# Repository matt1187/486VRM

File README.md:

# Project  486VRM.
A interposer for  3.3V 486  for using on motherboard without 3.3V regulator.
A advantage of this  486VRM interposer: switching regulator instead linear regulator. -> less heating.

# PCB Revision History
- 000 initial draft
- 001 smaller pcb size, current limit resistor added for Intel DX4 I/O buffer (pin J1), added solder help

# Feartures
- Vcore can be adjusting with jumper: 3.3V,  3.45 and 4V
- Clock-Multi jumper (for some DX4 and AMD/Cyrix 5x86)
- Writeback L1 jumper 
- connector for fan, 5V

# Pictures & how to soldering of pin
- I use "BGA"-technologie on this interposer.

- using of solder paste is very recommend.
- you need solder iron with long and small chisel for extra adding of tin to socket.

- "solder helper hold pin (bottom) on their place.
- very recommend: solder only one row with pin to pcb, then second row, then third row.

# Bill of material
[

|Footprint|Count|Value|Supplier|Order-number|
|--------------|----|-----|-------|-----------------|
|Top1|1|486|various|PGA-168 486 168pin socket|
|Bot1|1|486|various| turned pin header, dia =0.5mm|
|JP1|1|WB/WT|Digikey|609-78511-203HLF-ND|
|JP2|1|voltage|Digikey|609-78511-203HLF-ND|
|JP3|1|CLKMUL|Digikey|609-78511-203HLF-ND|
|JP4|1|FAN|Digikey|609-78511-203HLF-ND|
|U1|1|TPS54308DDCR|Digikey|296-47880-1-ND|
|R1|1|50Ω|Digikey|541-CRCW080550R0FKTACT-ND |
|R2|1|100kΩ|Digikey|311-100KARCT-ND |
|R3|1|22kΩ|Digikey|311-22KARCT-ND|
|R4|1|430kΩ|Digikey|311-430KARCT-ND |
|R5|1|91kΩ|Digikey|311-91KARCT-ND |
|R6|1|100Ω|Digikey|603-RC0805JR-07100RL|
|C4,C3,C2,C1|4|10µF|Digikey|399-C1206C106M3PAC7210CT-ND |
|C6|1|75pf|Digikey|478-3743-1-ND|
|C10,C9,C8,C7,C5|5|0.1µF|Digikey|KGM21NR71H104KT|
|C11|1|47µF|Digikey|T491C476M010AT|
|L1|1|10µh|Digikey|LMLP07A7M100DTAS |

# License
The project is free for non-commercial reproduction. Do not sell it on Ebay or other platforms for profit. Do not make a closed source derivative. Share your experiences and ideas with the community.

This work is licensed under a [Creative Commons Attribution-NonCommercial-ShareAlike 4.0 International License][cc-by-nc-sa].

[![CC BY-NC-SA 4.0][cc-by-nc-sa-image]][cc-by-nc-sa]

[cc-by-nc-sa]: http://creativecommons.org/licenses/by-nc-sa/4.0/
[cc-by-nc-sa-image]: https://licensebuttons.net/l/by-nc-sa/4.0/88x31.png

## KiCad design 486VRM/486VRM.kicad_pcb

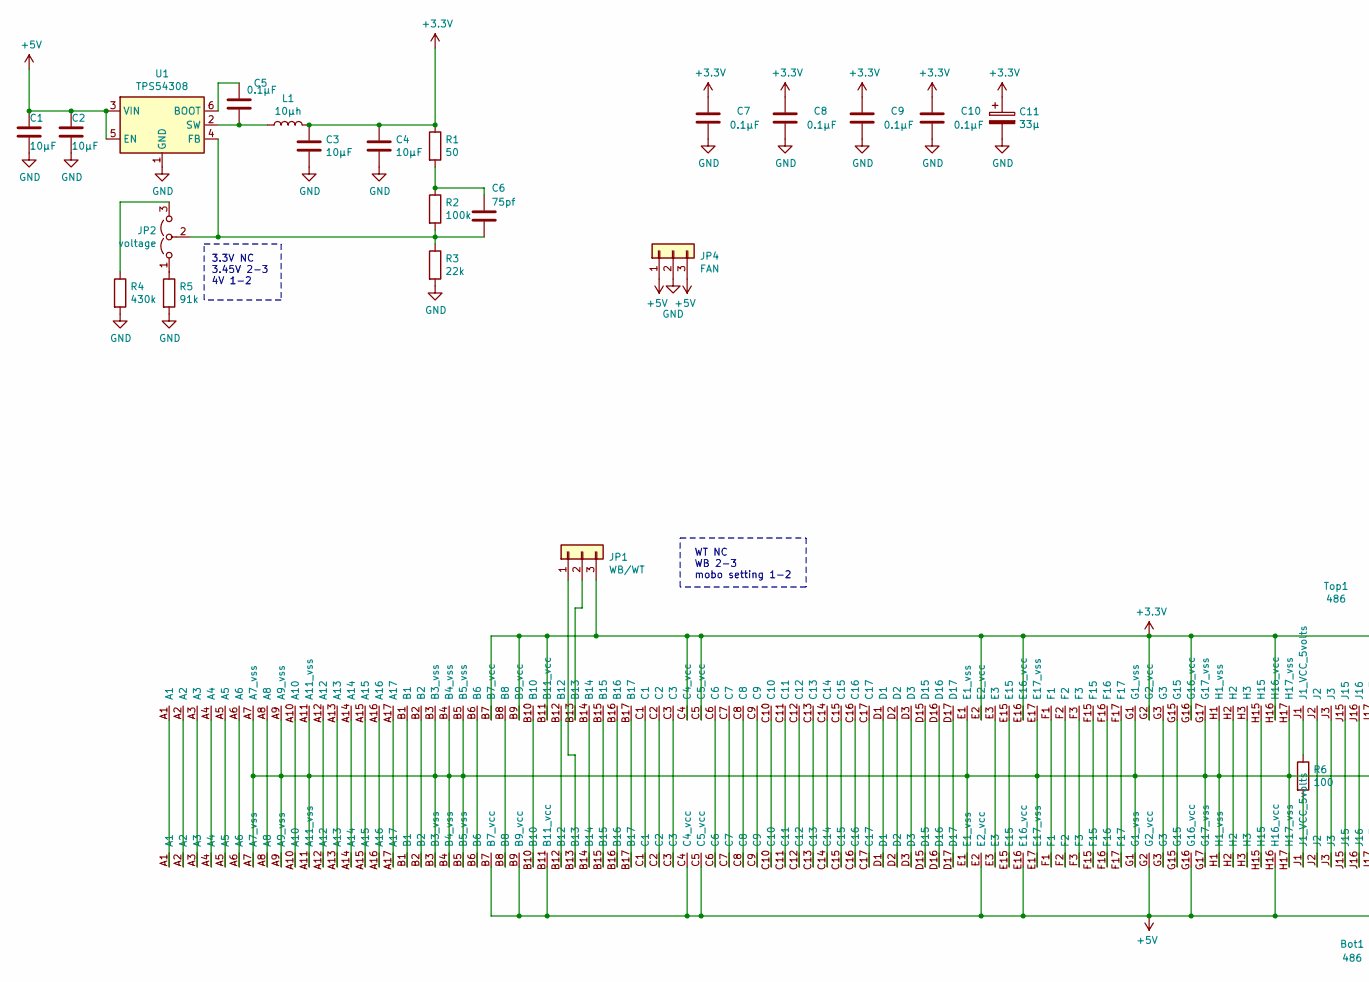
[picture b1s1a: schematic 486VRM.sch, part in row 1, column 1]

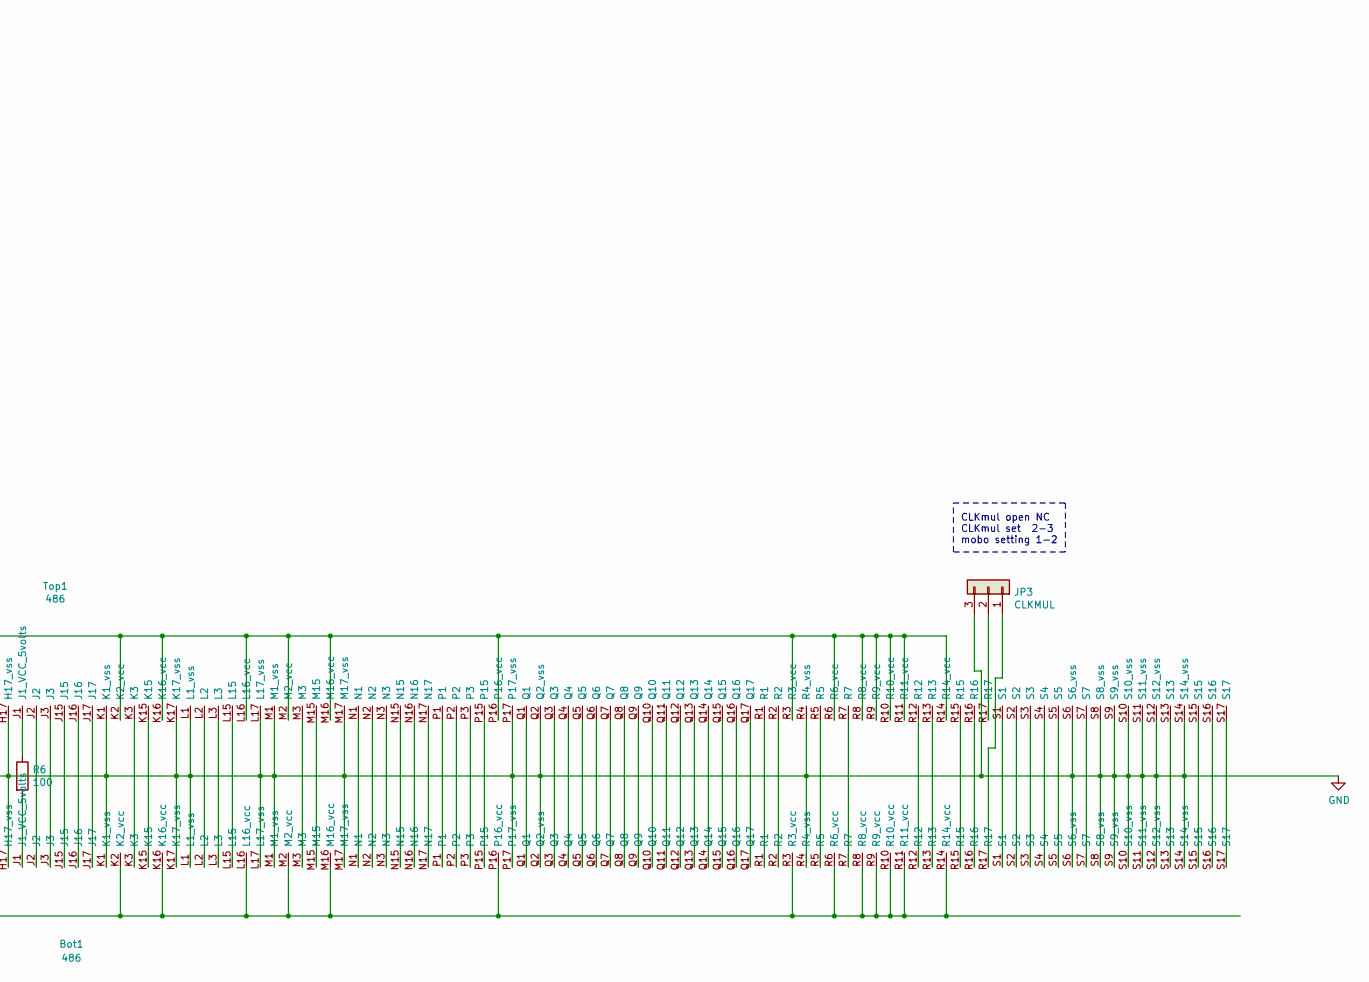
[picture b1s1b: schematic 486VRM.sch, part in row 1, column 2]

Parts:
Bot1: 486; PGA-168_Socket
C1, C2, C3, C4: 10µF; C_1206_3216Metric
C5, C7, C8, C9, C10: 0.1µF; C_0805_2012Metric
C6: 75pf; C_0805_2012Metric
C11: 33µ; CP_EIA-6032-15_Kemet-U
JP1: WB/WT; PinHeader_1x03_P2.54mm_Vertical
JP2: voltage; PinHeader_1x03_P2.54mm_Vertical
JP3: CLKMUL; PinHeader_1x03_P2.54mm_Vertical
JP4: FAN; PinHeader_1x03_P2.54mm_Vertical
L1: 10µh; L_Taiyo-Yuden_NR-80xx
R1: 50; R_0805_2012Metric
R2: 100k; R_0805_2012Metric
R3: 22k; R_0805_2012Metric
R4: 430k; R_0805_2012Metric
R5: 91k; R_0805_2012Metric
R6: 100; R_0805_2012Metric
Top1: 486; PGA-168
U1: TPS54308; SOT-23-6

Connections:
+3V3: C3.1, C4.1, C7.1, C8.1, C9.1, C10.1, C11.1, JP1.3, L1.2, R1.1, Top1.B7 (B7_vcc), Top1.B9 (B9_vcc), Top1.B11 (B11_vcc), Top1.C4 (C4_vcc), Top1.C5 (C5_vcc), Top1.E2 (E2_vcc), Top1.E16 (E16_vcc), Top1.G2 (G2_vcc), Top1.G16 (G16_vcc), Top1.H16 (H16_vcc), Top1.K2 (K2_vcc), Top1.K16 (K16_vcc), Top1.L16 (L16_vcc), Top1.M2 (M2_vcc), Top1.M16 (M16_vcc), Top1.P16 (P16_vcc), Top1.R3 (R3_vcc), Top1.R6 (R6_vcc), Top1.R8 (R8_vcc), Top1.R9 (R9_vcc), Top1.R10 (R10_vcc), Top1.R11 (R11_vcc), Top1.R14 (R14_vcc)
+5V: Bot1.B7 (B7_vcc), Bot1.B9 (B9_vcc), Bot1.B11 (B11_vcc), Bot1.C4 (C4_vcc), Bot1.C5 (C5_vcc), Bot1.E2 (E2_vcc), Bot1.E16 (E16_vcc), Bot1.G2 (G2_vcc), Bot1.G16 (G16_vcc), Bot1.H16 (H16_vcc), Bot1.K2 (K2_vcc), Bot1.K16 (K16_vcc), Bot1.L16 (L16_vcc), Bot1.M2 (M2_vcc), Bot1.M16 (M16_vcc), Bot1.P16 (P16_vcc), Bot1.R3 (R3_vcc), Bot1.R6 (R6_vcc), Bot1.R8 (R8_vcc), Bot1.R9 (R9_vcc), Bot1.R10 (R10_vcc), Bot1.R11 (R11_vcc), Bot1.R14 (R14_vcc), C1.1, C2.1, JP4.1, JP4.3, U1.3 (VIN), U1.5 (EN)
GND: Bot1.A7 (A7_vss), Bot1.A9 (A9_vss), Bot1.A11 (A11_vss), Bot1.B3 (B3_vss), Bot1.B4 (B4_vss), Bot1.B5 (B5_vss), Bot1.E1 (E1_vss), Bot1.E17 (E17_vss), Bot1.G1 (G1_vss), Bot1.G17 (G17_vss), Bot1.H1 (H1_vss), Bot1.H17 (H17_vss), Bot1.K1 (K1_vss), Bot1.K17 (K17_vss), Bot1.L1 (L1_vss), Bot1.L17 (L17_vss), Bot1.M1 (M1_vss), Bot1.M17 (M17_vss), Bot1.P17 (P17_vss), Bot1.Q2 (Q2_vss), Bot1.R4 (R4_vss), Bot1.S6 (S6_vss), Bot1.S8 (S8_vss), Bot1.S9 (S9_vss), Bot1.S10 (S10_vss), Bot1.S11 (S11_vss), Bot1.S12 (S12_vss), Bot1.S14 (S14_vss), C1.2, C2.2, C3.2, C4.2, C7.2, C8.2, C9.2, C10.2, C11.2, JP3.3, JP4.2, R3.2, R4.2, R5.2, Top1.A7 (A7_vss), Top1.A9 (A9_vss), Top1.A11 (A11_vss), Top1.B3 (B3_vss), Top1.B4 (B4_vss), Top1.B5 (B5_vss), Top1.E1 (E1_vss), Top1.E17 (E17_vss), Top1.G1 (G1_vss), Top1.G17 (G17_vss), Top1.H1 (H1_vss), Top1.H17 (H17_vss), Top1.K1 (K1_vss), Top1.K17 (K17_vss), Top1.L1 (L1_vss), Top1.L17 (L17_vss), Top1.M1 (M1_vss), Top1.M17 (M17_vss), Top1.P17 (P17_vss), Top1.Q2 (Q2_vss), Top1.R4 (R4_vss), Top1.S6 (S6_vss), Top1.S8 (S8_vss), Top1.S9 (S9_vss), Top1.S10 (S10_vss), Top1.S11 (S11_vss), Top1.S12 (S12_vss), Top1.S14 (S14_vss), U1.1 (GND)
unnamed: Bot1.A1, Top1.A1
unnamed: Bot1.A2, Top1.A2
unnamed: Bot1.A3, Top1.A3
unnamed: Bot1.A4, Top1.A4
unnamed: Bot1.A5, Top1.A5
unnamed: Bot1.A6, Top1.A6
unnamed: Bot1.A8, Top1.A8
unnamed: Bot1.A10, Top1.A10
unnamed: Bot1.A12, Top1.A12
unnamed: Bot1.A13, Top1.A13
unnamed: Bot1.A14, Top1.A14
unnamed: Bot1.A15, Top1.A15
unnamed: Bot1.A16, Top1.A16
unnamed: Bot1.A17, Top1.A17
unnamed: Bot1.B1, Top1.B1
unnamed: Bot1.B2, Top1.B2
unnamed: Bot1.B6, Top1.B6
unnamed: Bot1.B8, Top1.B8
unnamed: Bot1.B10, Top1.B10
unnamed: Bot1.B12, Top1.B12
unnamed: Bot1.B13, JP1.1
unnamed: Bot1.B14, Top1.B14
unnamed: Bot1.B15, Top1.B15
unnamed: Bot1.B16, Top1.B16
unnamed: Bot1.B17, Top1.B17
unnamed: Bot1.C1, Top1.C1
unnamed: Bot1.C2, Top1.C2
unnamed: Bot1.C3, Top1.C3
unnamed: Bot1.C6, Top1.C6
unnamed: Bot1.C7, Top1.C7
unnamed: Bot1.C8, Top1.C8
unnamed: Bot1.C9, Top1.C9
unnamed: Bot1.C10, Top1.C10
unnamed: Bot1.C11, Top1.C11
unnamed: Bot1.C12, Top1.C12
unnamed: Bot1.C13, Top1.C13
unnamed: Bot1.C14, Top1.C14
unnamed: Bot1.C15, Top1.C15
unnamed: Bot1.C16, Top1.C16
unnamed: Bot1.C17, Top1.C17
unnamed: Bot1.D1, Top1.D1
unnamed: Bot1.D2, Top1.D2
unnamed: Bot1.D3, Top1.D3
unnamed: Bot1.D15, Top1.D15
unnamed: Bot1.D16, Top1.D16
unnamed: Bot1.D17, Top1.D17
unnamed: Bot1.E3, Top1.E3
unnamed: Bot1.E15, Top1.E15
unnamed: Bot1.F1, Top1.F1
unnamed: Bot1.F2, Top1.F2
unnamed: Bot1.F3, Top1.F3
unnamed: Bot1.F15, Top1.F15
unnamed: Bot1.F16, Top1.F16
unnamed: Bot1.F17, Top1.F17
unnamed: Bot1.G3, Top1.G3
unnamed: Bot1.G15, Top1.G15
unnamed: Bot1.H2, Top1.H2
unnamed: Bot1.H3, Top1.H3
unnamed: Bot1.H15, Top1.H15
unnamed: Bot1.J1 (J1_VCC_5volts), R6.2
unnamed: Bot1.J2, Top1.J2
unnamed: Bot1.J3, Top1.J3
unnamed: Bot1.J15, Top1.J15
unnamed: Bot1.J16, Top1.J16
unnamed: Bot1.J17, Top1.J17
unnamed: Bot1.K3, Top1.K3
unnamed: Bot1.K15, Top1.K15
unnamed: Bot1.L2, Top1.L2
unnamed: Bot1.L3, Top1.L3
unnamed: Bot1.L15, Top1.L15
unnamed: Bot1.M3, Top1.M3
unnamed: Bot1.M15, Top1.M15
unnamed: Bot1.N1, Top1.N1
unnamed: Bot1.N2, Top1.N2
unnamed: Bot1.N3, Top1.N3
unnamed: Bot1.N15, Top1.N15
unnamed: Bot1.N16, Top1.N16
unnamed: Bot1.N17, Top1.N17
unnamed: Bot1.P1, Top1.P1
unnamed: Bot1.P2, Top1.P2
unnamed: Bot1.P3, Top1.P3
unnamed: Bot1.P15, Top1.P15
unnamed: Bot1.Q1, Top1.Q1
unnamed: Bot1.Q3, Top1.Q3
unnamed: Bot1.Q4, Top1.Q4
unnamed: Bot1.Q5, Top1.Q5
unnamed: Bot1.Q6, Top1.Q6
unnamed: Bot1.Q7, Top1.Q7
unnamed: Bot1.Q8, Top1.Q8
unnamed: Bot1.Q9, Top1.Q9
unnamed: Bot1.Q10, Top1.Q10
unnamed: Bot1.Q11, Top1.Q11
unnamed: Bot1.Q12, Top1.Q12
unnamed: Bot1.Q13, Top1.Q13
unnamed: Bot1.Q14, Top1.Q14
unnamed: Bot1.Q15, Top1.Q15
unnamed: Bot1.Q16, Top1.Q16
unnamed: Bot1.Q17, Top1.Q17
unnamed: Bot1.R1, Top1.R1
unnamed: Bot1.R2, Top1.R2
unnamed: Bot1.R5, Top1.R5
unnamed: Bot1.R7, Top1.R7
unnamed: Bot1.R12, Top1.R12
unnamed: Bot1.R13, Top1.R13
unnamed: Bot1.R15, Top1.R15
unnamed: Bot1.R16, Top1.R16
unnamed: Bot1.R17, JP3.1
unnamed: Bot1.S1, Top1.S1
unnamed: Bot1.S2, Top1.S2
unnamed: Bot1.S3, Top1.S3
unnamed: Bot1.S4, Top1.S4
unnamed: Bot1.S5, Top1.S5
unnamed: Bot1.S7, Top1.S7
unnamed: Bot1.S13, Top1.S13
unnamed: Bot1.S15, Top1.S15
unnamed: Bot1.S16, Top1.S16
unnamed: Bot1.S17, Top1.S17
unnamed: C5.1, U1.6 (BOOT)
unnamed: C5.2, L1.1, U1.2 (SW)
unnamed: C6.1, R1.2, R2.1
unnamed: C6.2, JP2.2 (C), R2.2, R3.1, U1.4 (FB)
unnamed: JP1.2, Top1.B13
unnamed: JP2.1 (A), R5.1
unnamed: JP2.3 (B), R4.1
unnamed: JP3.2, Top1.R17
unnamed: R6.1, Top1.J1 (J1_VCC_5volts)

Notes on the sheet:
3.3V NC 3.45V 2-3 4V 1-2
WT NC WB 2-3 mobo setting 1-2
CLKmul open NC CLKmul set 2-3 mobo setting 1-2

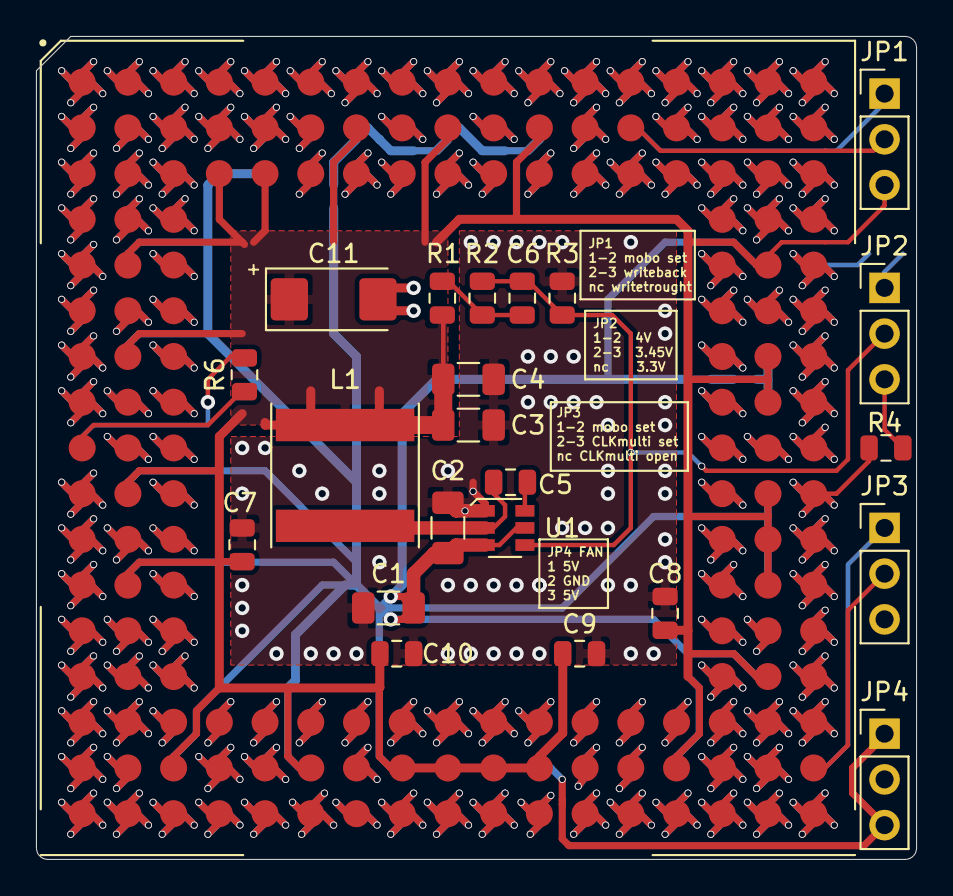
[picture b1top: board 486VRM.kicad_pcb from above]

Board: 2 copper layers, 48.9 x 45.7 mm, 25 parts (1 on the bottom side), 129 nets.

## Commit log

2024-01-01 Rename Schaltplan.pdf to schematic.pdf
2024-05-07 Update README.md
    added license
2024-05-07 Add files via upload
    added file license
